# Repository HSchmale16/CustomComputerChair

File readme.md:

# Custom Computer Chair #
This project is a custom computer chair with a
custom mouse and keyboard implemented.

# Notes #
* The schematic and PCB Files are viewed with the KiCad software package
which is free software.

# Resources #
This project includes code from the following sources
* Adafruit's 5v USB Trinkey Mouse and Keyboard Library
* USBDRV

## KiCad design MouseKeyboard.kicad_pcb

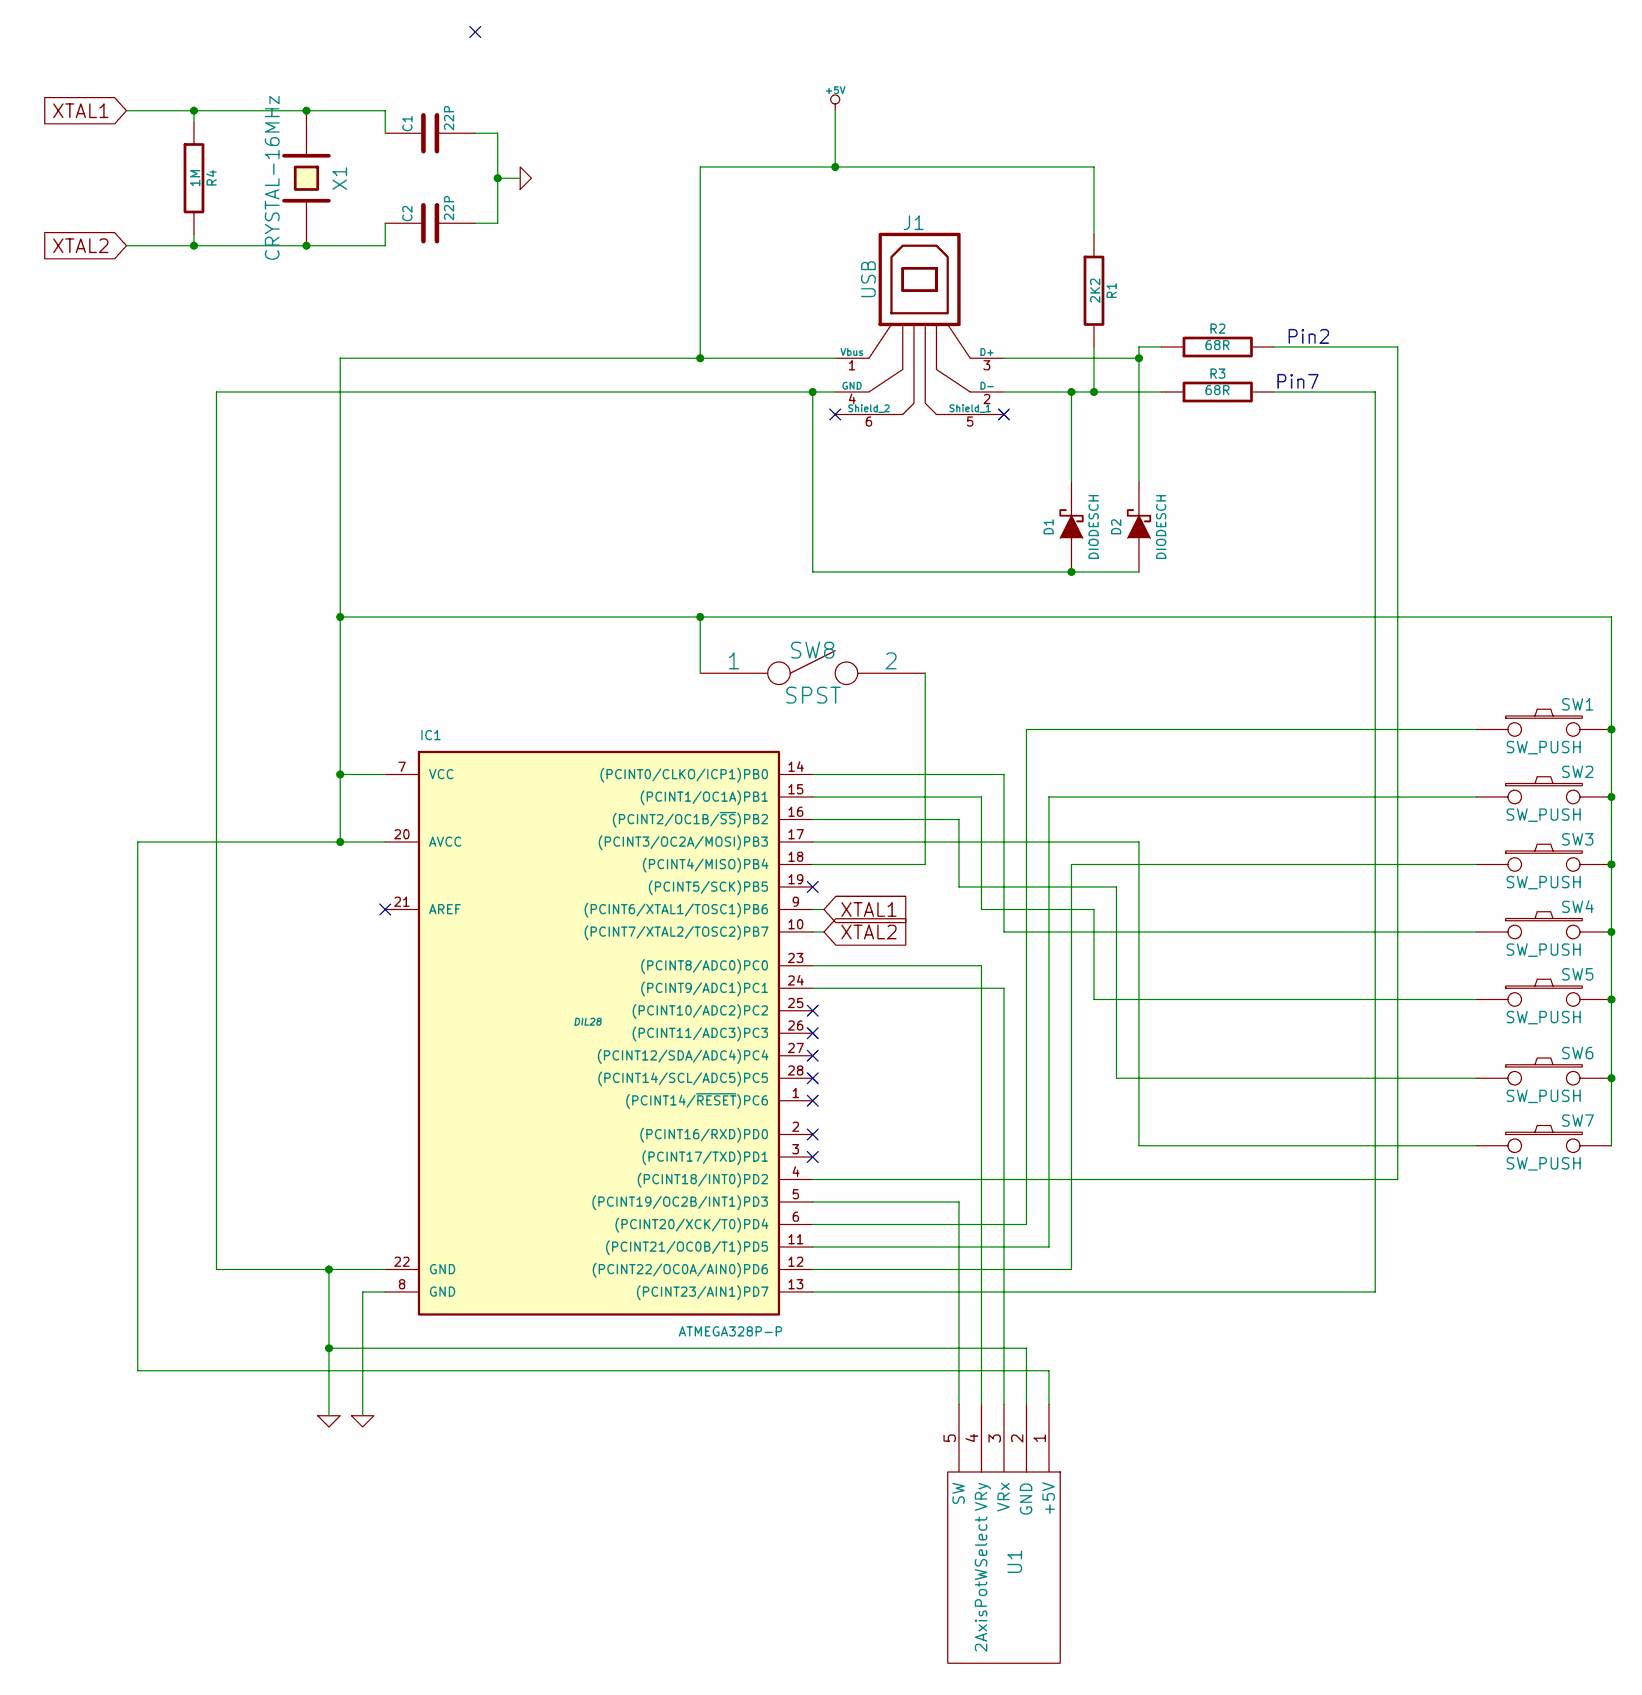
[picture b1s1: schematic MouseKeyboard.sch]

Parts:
C1, C2: 22P
D1, D2: DIODESCH
IC1: ATMEGA328P-P; DIL28
J1: USB
R1: 2K2
R2, R3: 68R
R4: 1M
SW1, SW2, SW3, SW4, SW5, SW6, SW7: SW_PUSH
SW8: SPST
U1: 2AxisPotWSelect
X1: CRYSTAL-16MHz

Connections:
+5V: IC1.7 (VCC), IC1.20 (AVCC), J1.1 (Vbus), R1.1, SW1.2, SW2.2, SW3.2, SW4.2, SW5.2, SW6.2, SW7.2, SW8.1, U1.1 (+5V)
GND: C1.2, C2.2, D1.1 (A), D2.1 (A), IC1.8 (GND), IC1.22 (GND), J1.4 (GND), U1.2 (GND)
unnamed: D1.2 (K), J1.2 (D-), R1.2, R3.1
unnamed: D2.2 (K), J1.3 (D+), R2.1
unnamed: IC1.4 ((PCINT18/INT0)PD2), R2.2
unnamed: IC1.5 ((PCINT19/OC2B/INT1)PD3), U1.5 (SW)
unnamed: IC1.6 ((PCINT20/XCK/T0)PD4), SW1.1
unnamed: IC1.11 ((PCINT21/OC0B/T1)PD5), SW2.1
unnamed: IC1.12 ((PCINT22/OC0A/AIN0)PD6), SW3.1
unnamed: IC1.13 ((PCINT23/AIN1)PD7), R3.2
unnamed: IC1.14 ((PCINT0/CLKO/ICP1)PB0), SW4.1
unnamed: IC1.15 ((PCINT1/OC1A)PB1), SW5.1
unnamed: IC1.16 ((PCINT2/OC1B/~SS~)PB2), SW6.1
unnamed: IC1.17 ((PCINT3/OC2A/MOSI)PB3), SW7.1
unnamed: IC1.18 ((PCINT4/MISO)PB4), SW8.2
unnamed: IC1.23 ((PCINT8/ADC0)PC0), U1.4 (VRy)
unnamed: IC1.24 ((PCINT9/ADC1)PC1), U1.3 (VRx)
XTAL1: C1.1, IC1.9 ((PCINT6/XTAL1/TOSC1)PB6), R4.1, X1.1
XTAL2: C2.1, IC1.10 ((PCINT7/XTAL2/TOSC2)PB7), R4.2, X1.2

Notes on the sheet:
Pin2
Pin7

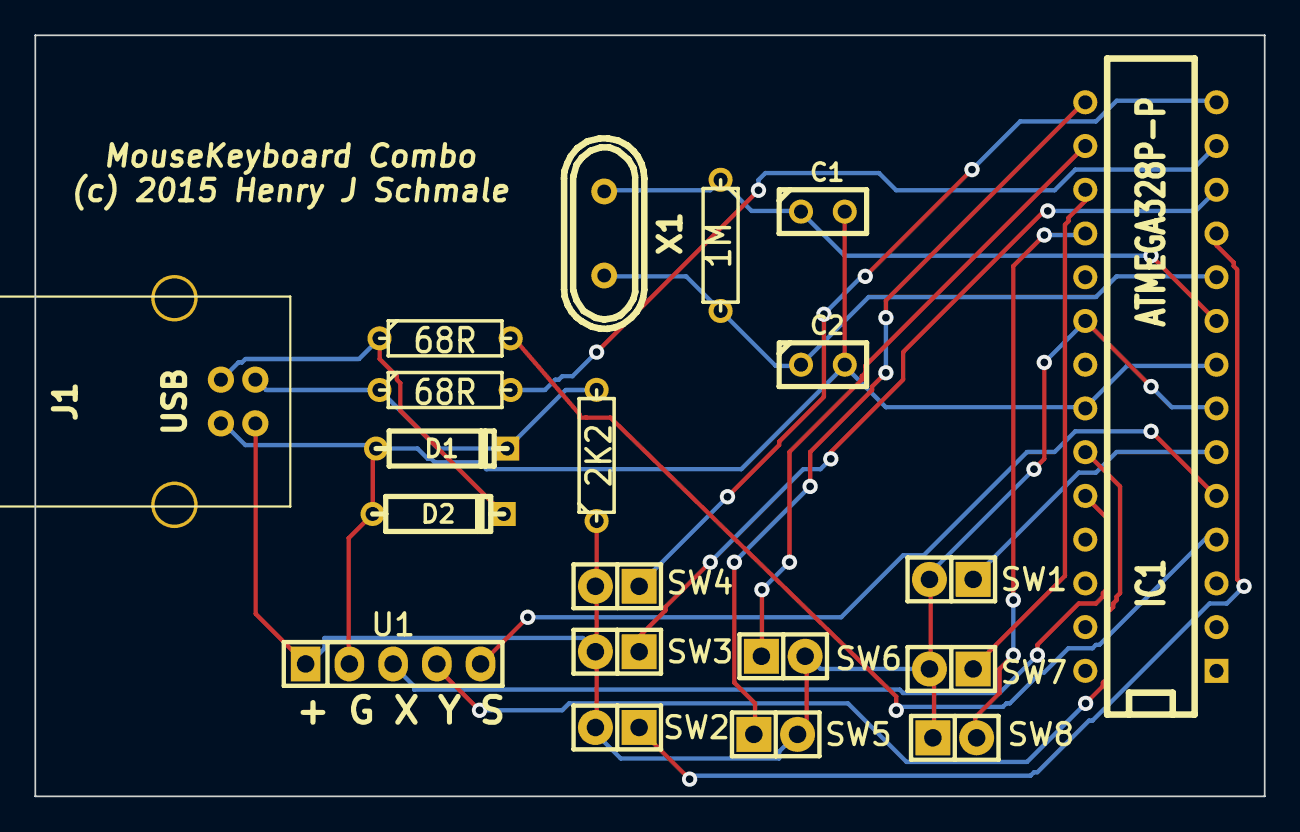
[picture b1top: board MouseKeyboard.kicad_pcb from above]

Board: 2 copper layers, 71.4 x 44.2 mm, 20 parts (0 on the bottom side), 19 nets.

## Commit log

2015-02-10 Initial Commit
    * Readme.md
    * Arduino Sketch Started
2015-02-10 Renamed Arduino Sketch
2015-02-10 Finished Documentation block of Arduino Sketch
2015-02-11 Selective Compilation
2015-02-11 Started Drawing the schematic
2015-02-11 Placed Most of the componets
2015-02-11 Just found out that I don't need a 32u4 microcontroller to make this work
2015-02-11 Updates
    * Constants Declared
    * Switched to AVR ATMega328 in schematic
2015-02-11 Added a gitignore
2015-02-11 Updated Schematic
    Started a codeblocks project for this
2015-02-11 Stupid Object file got into version control
2015-02-11 Updated GitIgnore to prevent build & other garbage files from getting into version control.
2015-02-11 Codeblocks Idea Change
2015-02-11 Just got codeblocks set up for arduino
2015-02-11 New stuff
    * got rid of html build log, stupid codeblocks templetes
    * Made an upload script, b/c the upload command is really friggin long
    * Updated gitignore for html that doesn't belong
2015-02-11 No More Dirty Ugly Hacks!
2015-02-11 Stuff
2015-02-12 More Wires
2015-02-12 A Constants Header is added
2015-02-12 Started Laying out keyboard matrix
2015-02-12 New Code Files
    * Codified the some files
    * Finished typing out the keyboard matrix
    * Added files to contain primary implementation
2015-02-12 New Files in project
    * Implementation files and whatnot
2015-02-12 New Constants
    * Set up keyboard matrix to use constants
2015-02-12 End of the day commit
    * Constants & Stuff
2015-02-12 New Files
    * Using Adafruit's Trinket HID Combo Modded to my own needs for
    controlling keyboard.
2015-02-13 Did stuff
    * Added to constants
    * Fixed up the usbconfig
    * Started working on main
2015-02-13 Fixed GitIgnore to ignore doxyblocks
2015-02-13 Stuff
    * A loop for execution
2015-02-13 Started Filling out the usb port
2015-02-13 Replace Trinket With Pro-Trinket
2015-02-13 Constants
    * Constants in header
    * USB Schematic
2015-02-13 Moved Diagram Around a bit
2015-02-13 Schematic is almost done
    YAY!
    Just have to make a bill of materials
2015-02-13 Net File
2015-02-13 Something
2015-02-13 Schematic Stuff
    * Moved some wires
2015-02-13 PCB Layout
    * Started PCB Layout
    * Started a joystick test for the arduino
2015-02-13 Working Joystick Prototype
    Ammendment:
    This is really important! The joystick switch pin must be configured as INPUT_PULLUP
2015-02-13 My schematic was terrible
    It's being redrawn by me
2015-02-13 Added to the schematic, switches, on/off, etc
2015-02-14 Changed Paper Size
2015-02-14 Schematic is almost complete!!!
    The schematic just needs to be annotated, and values added. Then it
    is done.
2015-02-14 Finished The Pcb Parts List
2015-02-14 Started Work on the PCB Design
2015-02-14 Just a commit
    Restarted Laying out pcb
2015-02-14 Finished Laying out the pcb
2015-02-14 Shrunk the PCB a bit
2015-02-14 Copper Infill
2015-02-14 Finished Layout, now if only it would print
2015-02-14 Made the schematic fit into an 8.5x11 sheet
2015-02-14 Modified Project File
2015-02-14 Did some stuff
2015-02-14 Did Stuff
    * Constants, Basic Init
2015-02-14 Created A Parts List Markdown
    * Parts List Research
    * Added to implementation
2015-02-14 A Makefile & a parts list
2015-02-15 Updated gitignore for generated documentation
2015-02-15 Commented The Schematic
2015-02-15 Commented the PCB Layout
2015-02-16 Removed Garbage Files
2015-02-16 Added Globals to MouseKeyboard Prog
2015-02-16 More Constants, Key testing order, that kind of stuff is now included
2015-02-16 More Constants Documentation
2015-02-16 Documented Constants some more
2015-02-17 Started to get stuff done
    * New Constants
2015-02-17 Added new updaters
2015-02-21 Improved PCB Design
    * Reduced Size of board by ~20%
    * Rerouted, and it passes the design check
2015-02-21 Added more notes to readme.
2015-02-21 Silkscreen More Stuff
2015-02-21 Added Heat Conduction Plates all over the place
2015-02-21 Ingnores
    * Ignore Generated SVG
    * More dimensions
2015-03-02 Removed a file that shouldn't be here
    I have no idea how that makefile got in here. That makefile is for
    something else entirely
2015-03-02 Shrunk the PCB Design
    * The PCB is roughly 20% Smaller than before
    * \todo fix autorouting errors
    * \todo perform DRC
2015-03-02 Improved PCB Design
    * Changed Text Size
    * Moved Text Around
    * DRC
    * Improoved Routing
    \todo Copper Infill
    \todo Dimensioning
2015-03-04 BoardDims
    * Dim'd the board
    * Board Cuts
    \todo, fix silkscreening
2015-03-04 Fixed SilkScreen
    * Moved the silkscreened labels around
    They were being covered by actual parts

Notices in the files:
MouseKeyboard.kicad_pcb:
(c) 2015 Henry J Schmale
